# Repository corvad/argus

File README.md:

# Argus
My new public monorepo.

## Build
```bazel build //...```

## Regen build files
```bazel run //:gazelle```

## Generate .pb.go in place (fixes issues with autocomplete and go mod)
```./scripts/sync_proto.sh```

## Add license headers
```./scripts/license.sh```

## Run go mod tidy
```./scripts/mod_tidy.sh```

## License
Project is under an MIT License.

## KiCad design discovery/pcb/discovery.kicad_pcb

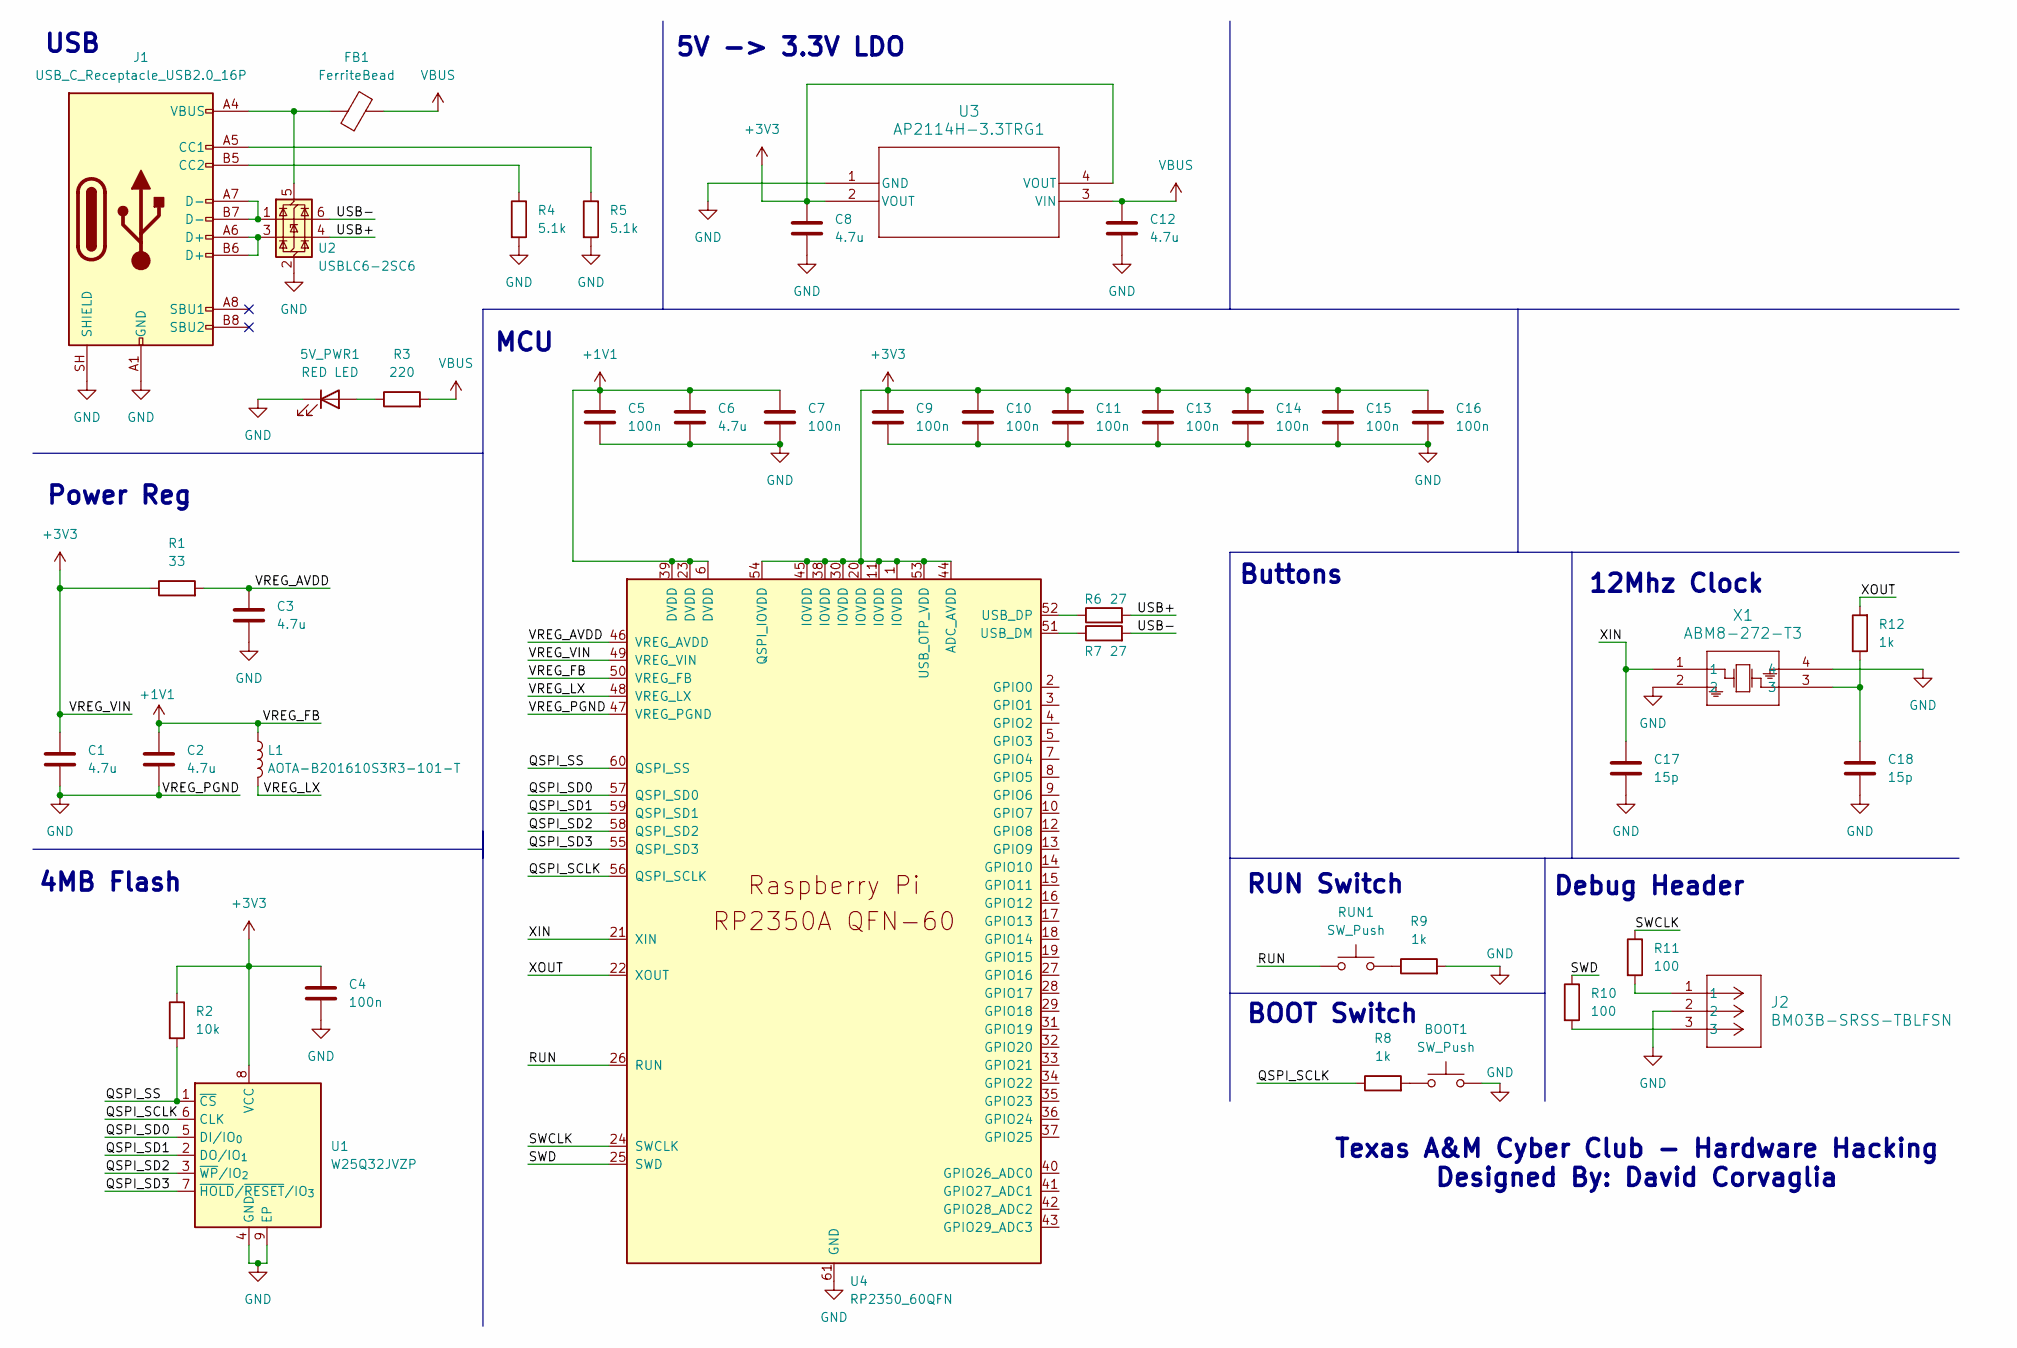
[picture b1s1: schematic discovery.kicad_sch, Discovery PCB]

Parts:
5V_PWR1: RED LED; LED_0603_1608Metric; LCSC C2286
BOOT1: SW_Push; SW_Push_1P1T_XKB_TS-1187A; LCSC C318884
C1, C2: 4.7u; C_0402_1005Metric_small_pads; LCSC C23733
C3, C6, C8, C12: 4.7u; C_0402_1005Metric; LCSC C23733
C4: 100n; C_0402_1005Metric
C5, C7, C9, C10, C11, C13, C14, C15, C16: 100n; C_0402_1005Metric; LCSC C1525
C17, C18: 15p; C_0402_1005Metric
FB1: FerriteBead; LED_0603_1608Metric; LCSC C14709
J1: USB_C_Receptacle_USB2.0_16P; USB_C_Receptacle_GCT_USB4105-xx-A_16P_TopMnt_Horizontal; LCSC C2765186
J2: BM03B-SRSS-TBLFSN; CONN_BM03B-SRSS-TBLFSN_JST
L1: AOTA-B201610S3R3-101-T; L_pol_2016; LCSC C42411119
R1: 33; R_0402_1005Metric; LCSC C25105
R2: 10k; R_0402_1005Metric
R3: 220; R_0402_1005Metric; LCSC C25091
R4, R5: 5.1k; R_0402_1005Metric; LCSC C25905
R6, R7: 27; R_0402_1005Metric; LCSC C25100
R8, R9, R12: 1k; R_0402_1005Metric
R10, R11: 100; R_0402_1005Metric
RUN1: SW_Push; SW_Push_1P1T_XKB_TS-1187A; LCSC C318884
U1: W25Q32JVZP; WSON-8-1EP_6x5mm_P1.27mm_EP3.4x4.3mm
U2: USBLC6-2SC6; SOT-23-6; LCSC C7519
U3: AP2114H-3.3TRG1; SOT-223_DIO; LCSC C150716
U4: RP2350_60QFN; RP2350-QFN-60-1EP_7x7_P0.4mm_EP3.4x3.4mm_ThermalVias
X1: ABM8-272-T3; ABM8-272-T3_ABR

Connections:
+1V1: C2.1, C5.1, C6.1, C7.1, L1.1, U4.6 (DVDD), U4.23 (DVDD), U4.39 (DVDD), U4.50 (VREG_FB)
+3V3: C1.1, C4.1, C8.1, C9.1, C10.1, C11.1, C13.1, C14.1, C15.1, C16.1, R1.1, R2.1, U1.8 (VCC), U3.2 (VOUT), U3.4 (VOUT), U4.1 (IOVDD), U4.11 (IOVDD), U4.20 (IOVDD), U4.30 (IOVDD), U4.38 (IOVDD), U4.44 (ADC_AVDD), U4.45 (IOVDD), U4.49 (VREG_VIN), U4.53 (USB_OTP_VDD), U4.54 (QSPI_IOVDD)
/QSPI_SCLK: R8.1, U1.6 (CLK), U4.56 (QSPI_SCLK)
/QSPI_SD0: U1.5 (DI/IO_{0}), U4.57 (QSPI_SD0)
/QSPI_SD1: U1.2 (DO/IO_{1}), U4.59 (QSPI_SD1)
/QSPI_SD2: U1.3 (~WP/IO_{2}), U4.58 (QSPI_SD2)
/QSPI_SD3: U1.7 (~HOLD/~RESET/IO_{3}), U4.55 (QSPI_SD3)
/QSPI_SS: R2.2, U1.1 (~CS), U4.60 (QSPI_SS)
/RUN: RUN1.1, U4.26 (RUN)
/SWCLK: R11.1, U4.24 (SWCLK)
/SWD: R10.1, U4.25 (SWD)
/USB+: R6.2, U2.4 (I/O2)
/USB-: R7.2, U2.6 (I/O1)
/VREG_AVDD: C3.1, R1.2, U4.46 (VREG_AVDD)
/VREG_LX: L1.2, U4.48 (VREG_LX)
/XIN: C17.1, U4.21 (XIN), X1.1
/XOUT: R12.2, U4.22 (XOUT)
GND: 5V_PWR1.1 (K), BOOT1.2, C1.2, C2.2, C3.2, C4.2, C5.2, C6.2, C7.2, C8.2, C9.2, C10.2, C11.2, C12.2, C13.2, C14.2, C15.2, C16.2, C17.2, C18.2, J1.A1 (GND), J1.A12 (GND), J1.B1 (GND), J1.B12 (GND), J1.SH (SHIELD), J2.2, R4.2, R5.2, R9.2, U1.4 (GND), U1.9 (EP), U2.2 (GND), U3.1 (GND), U4.47 (VREG_PGND), U4.61 (GND), X1.2, X1.4
unnamed: 5V_PWR1.2 (A), R3.1
unnamed: BOOT1.1, R8.2
unnamed: C18.1, R12.1, X1.3
unnamed: J1.A5 (CC1), R5.1
unnamed: J1.B5 (CC2), R4.1
unnamed: J1.A6 (D+), J1.B6 (D+), U2.3 (I/O2)
unnamed: J1.A7 (D-), J1.B7 (D-), U2.1 (I/O1)
unnamed: J2.1, R11.2
unnamed: J2.3, R10.2
unnamed: R9.1, RUN1.2
unnamed: FB1.1, J1.A4 (VBUS), J1.A9 (VBUS), J1.B4 (VBUS), J1.B9 (VBUS), U2.5 (VBUS)
unnamed: R7.1, U4.51 (USB_DM)
unnamed: R6.1, U4.52 (USB_DP)
VBUS: C12.1, FB1.2, R3.2, U3.3 (VIN)

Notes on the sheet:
5V -> 3.3V LDO
Texas A&M Cyber Club - Hardware Hacking Designed By: David Corvaglia
Debug Header
MCU
BOOT Switch
USB
RUN Switch
12Mhz Clock
4MB Flash
Buttons
Power Reg

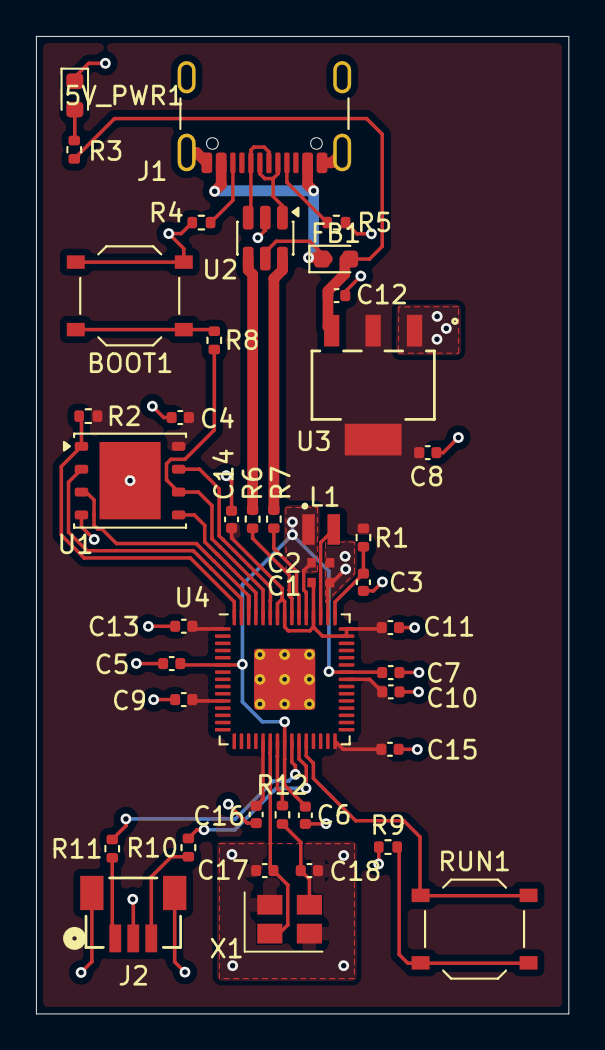
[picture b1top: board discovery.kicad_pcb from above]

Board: 2 copper layers, 29.6 x 54.3 mm, 42 parts (0 on the bottom side), 32 nets.

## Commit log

2026-03-31 add initial project
2026-03-31 add license
2026-03-31 format code and remove double license header
2026-03-31 Add initial README with project description and license
2026-03-31 Revise README for improved project overview
    Updated project description for clarity.
2026-03-31 Add GitHub Actions workflow for Go project build
2026-03-31 unset ANDROID_HOME
2026-03-31 add bazelisk cache github action
2026-03-31 update workflow name
2026-03-31 test blacksmith
2026-03-31 Update GitHub Actions workflow to simplify triggers
    Remove pull_request trigger and environment setting.
2026-03-31 Rename workflow from Build to CI Linux
2026-03-31 Update Bazelisk installation to specific version
2026-03-31 Replace curl with wget for Bazelisk installation
2026-03-31 Refactor CI workflow for Bazel build and GCP credentials
    Removed GCP authentication step and updated Bazel commands.
2026-03-31 Update CI workflow to use environment variables for secrets
2026-03-31 Change GCP_CREDENTIALS to GCS_BUCKET in ci-linux.yml
    Updated GCP_CREDENTIALS secret to GCS_BUCKET in CI workflow.
2026-03-31 populate changes to cache
2026-03-31 have bazel actually upload the artifacts
2026-03-31 fix gcp creds
2026-03-31 Change GCP_CREDENTIALS to GCP_BUCKET in CI config
    Updated GCP_CREDENTIALS secret to GCP_BUCKET in CI configuration.
2026-03-31 Update GCP credentials secret reference in CI config
2026-03-31 Add CI workflow for MacOS using Bazelisk
2026-03-31 Switch CI to macOS and modify Bazelisk installation
    Changed CI workflow to run on macOS and updated Bazelisk installation method.
2026-03-31 stupid ANDROID_SDK bazel stuff
2026-03-31 Change macOS runner to macos-latest-xlarge
2026-03-31 Change macOS runner to macos-latest
2026-03-31 add instructions to README.md
2026-03-31 Update README with new section for regen build files
2026-04-07 add logging proto
2026-04-07 proto: logging: use LogLevel enum in logging proto
2026-04-07 add logging utils
2026-04-09 Update README formatting and content
2026-04-14 add pcb
2026-04-14 add inductor
2026-04-14 make all components 0402 for the caps and resistors
2026-04-16 add rp2350 project
2026-04-16 fix uf2
